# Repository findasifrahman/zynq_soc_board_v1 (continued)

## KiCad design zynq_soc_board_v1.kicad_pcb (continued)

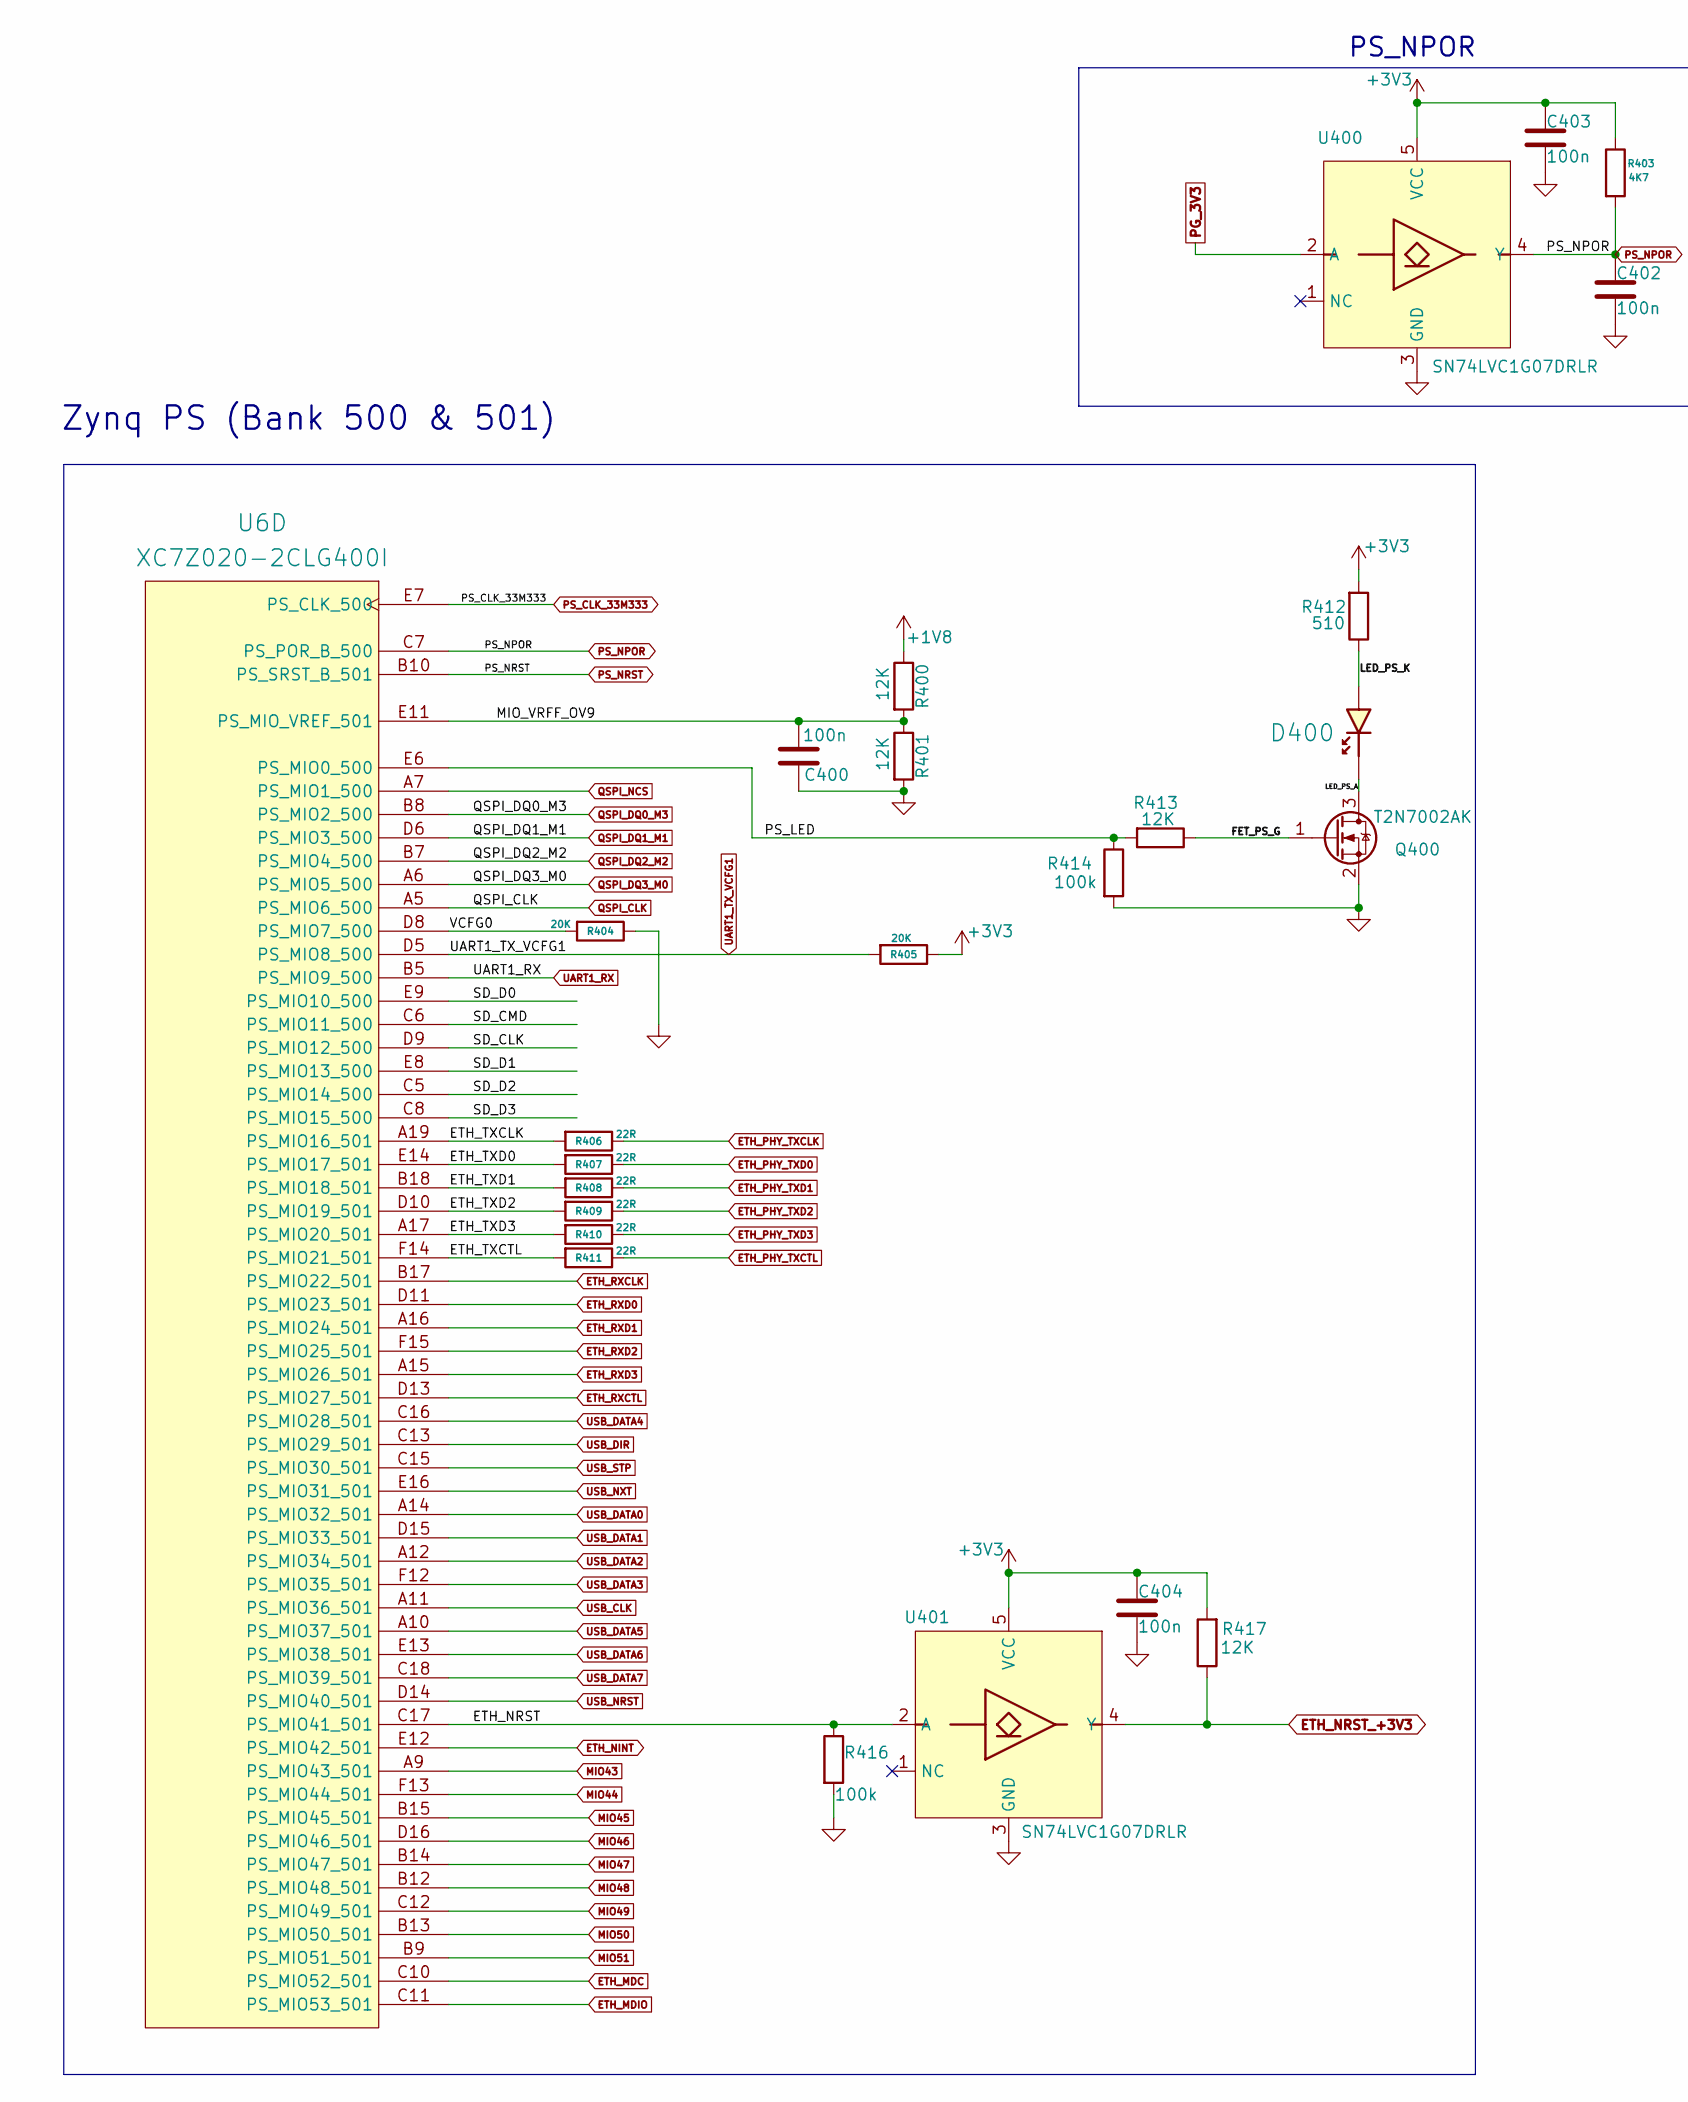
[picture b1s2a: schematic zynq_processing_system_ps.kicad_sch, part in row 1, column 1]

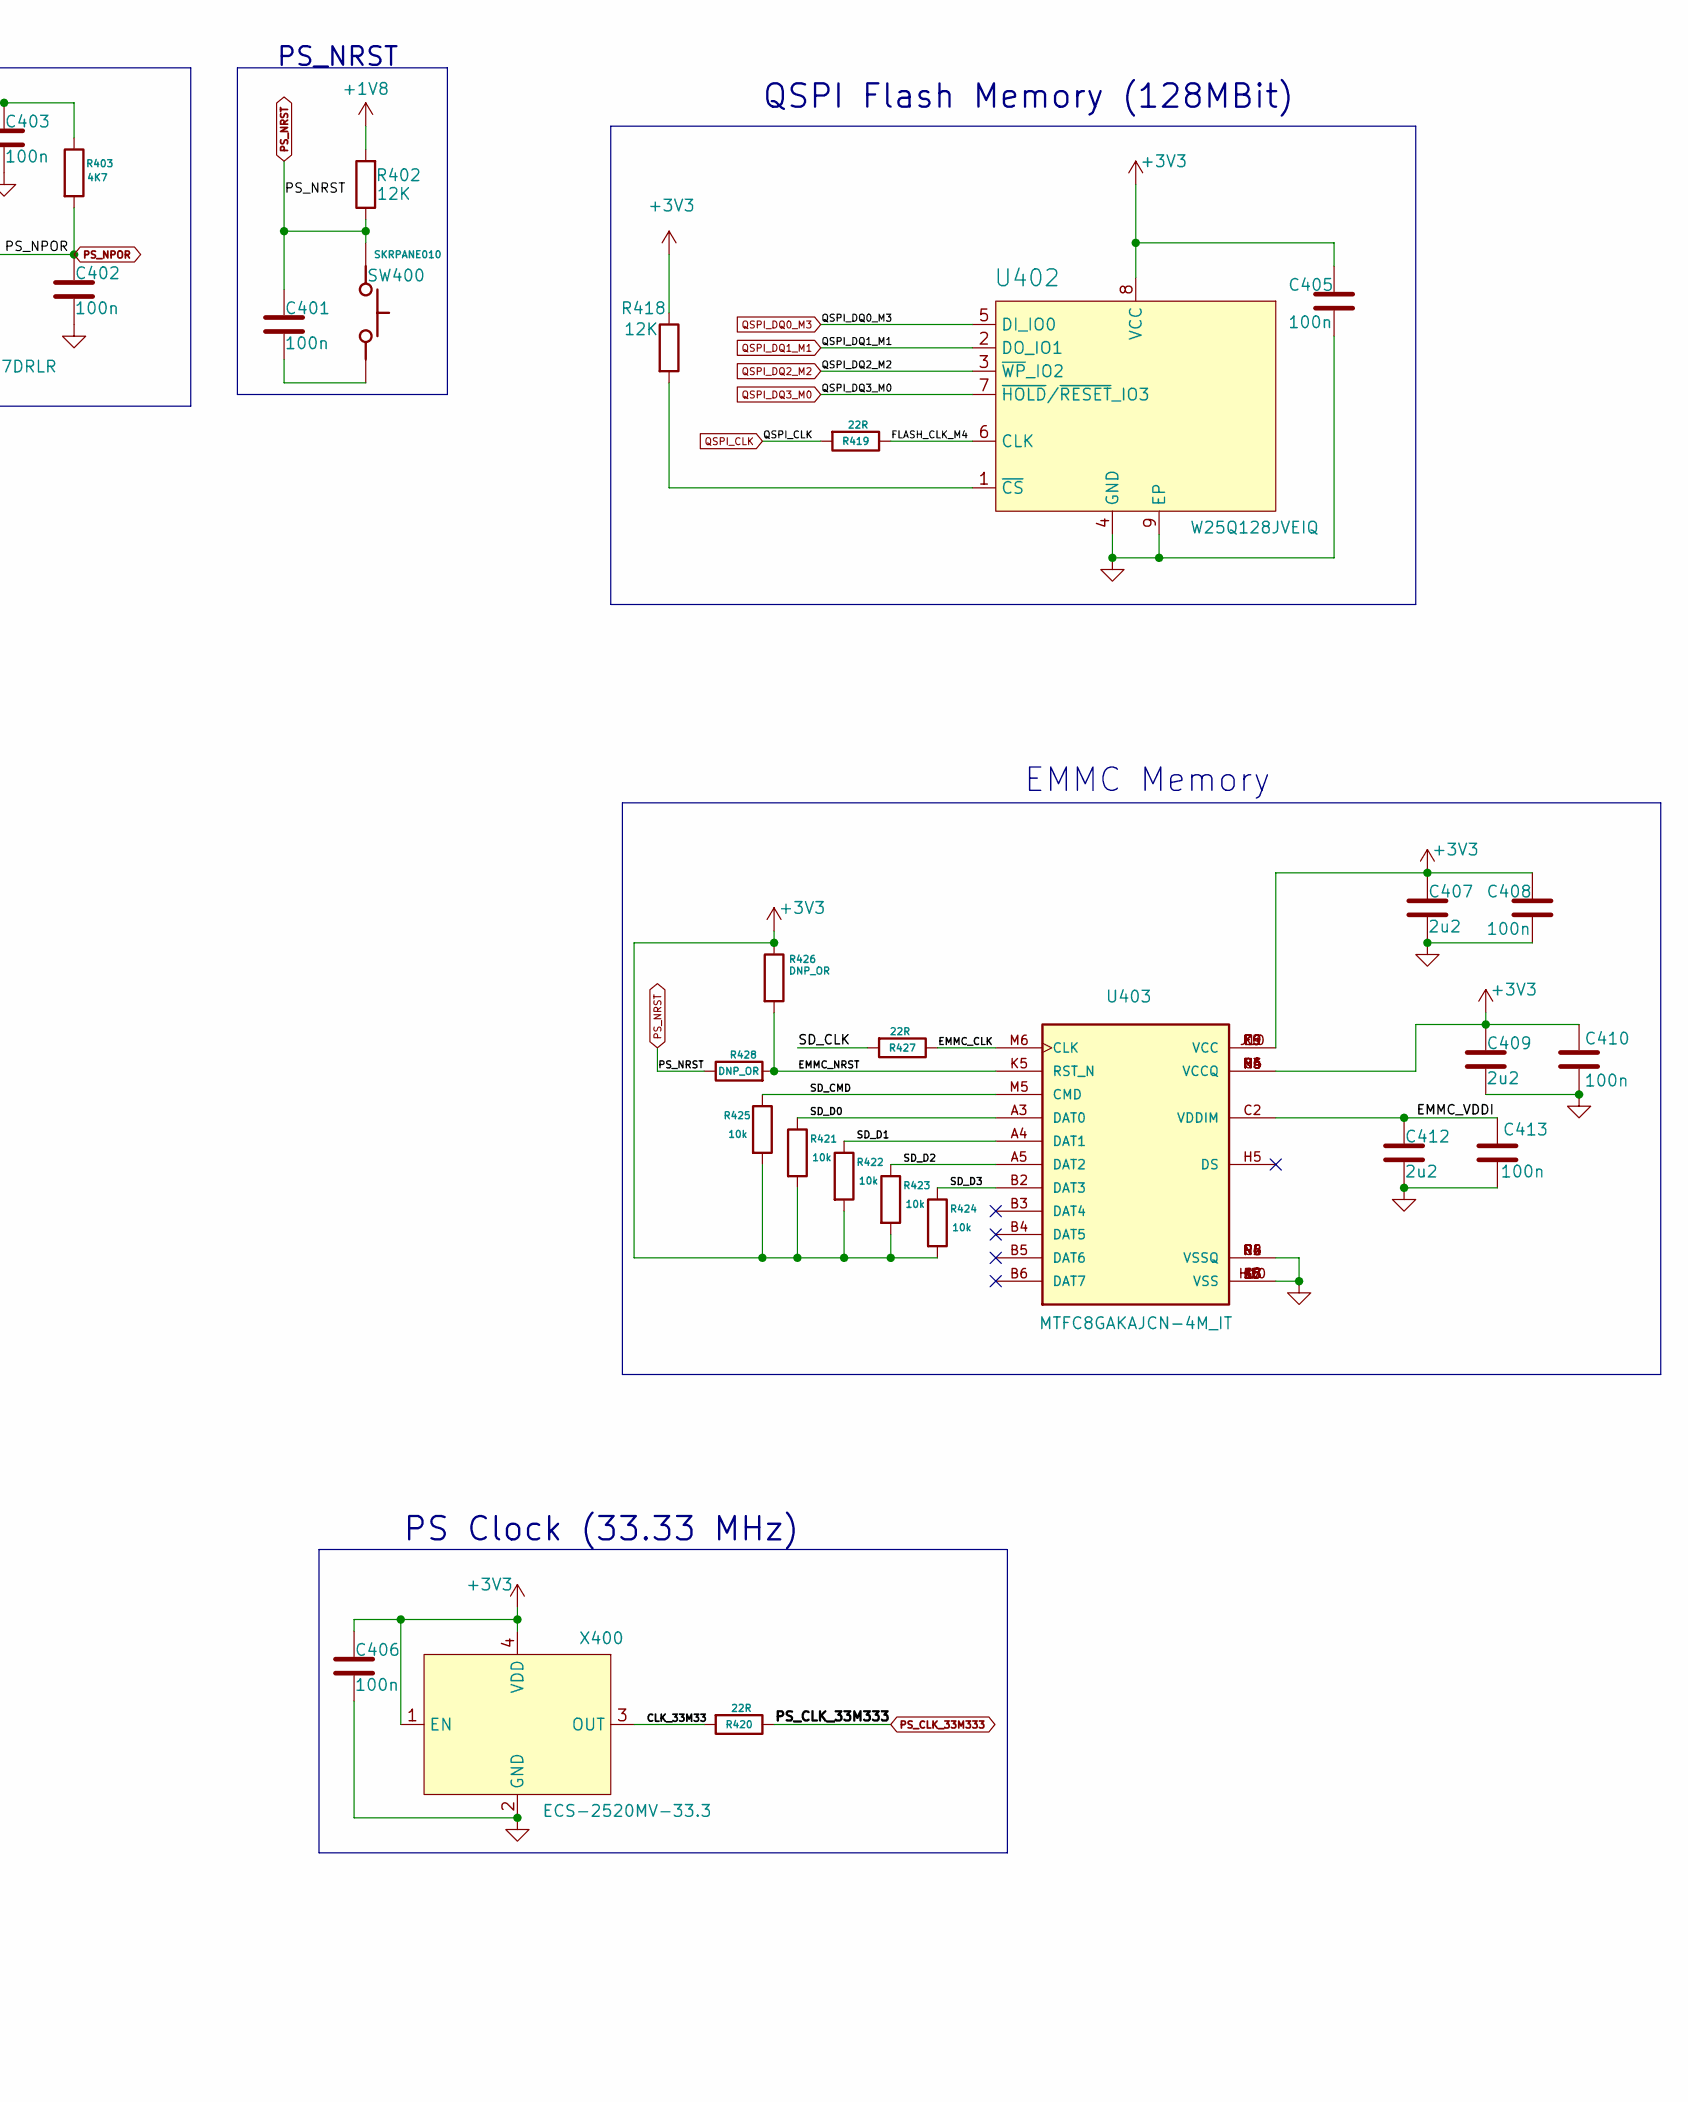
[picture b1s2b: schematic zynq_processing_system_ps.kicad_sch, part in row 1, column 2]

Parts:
C400, C401, C402, C403, C404, C405, C406, C408, C410, C413: 100n; C_0402_1005Metric; Manufacturer Part Number CL05B104KO5NNNC; LCSC C1525
C407, C409, C412: 2u2; C_0402_1005Metric; Manufacturer Part Number CL05A225MQ5NSNC; LCSC C12530
D400: RED; LED_0402_RED; Manufacturer Part Number NCD0402R1; LCSC C130719
Q400: T2N7002AK; SOT-23; Manufacturer Part Number T2N7002AK,LM; LCSC C516175
R400, R401, R402, R413, R417, R418: 12K; R_0402_1005Metric; Manufacturer Part Number 0402WGF1202TCE; LCSC C25752
R403: 4K7; R_0402_1005Metric; Manufacturer Part Number 0402WGF4701TCE; LCSC C25900
R404, R405: 20K; R0201; Manufacturer Part Number RC0201FR-0720KL; LCSC C295787
R406, R407, R408, R409, R410, R411, R419, R420, R427: 22R; R_0402_1005Metric; Manufacturer Part Number 0402WGF220JTCE; LCSC C25092
R412: 510; R_0402_1005Metric; Manufacturer Part Number RC-02W511JT; LCSC C1119
R414, R416: 100k; R_0402_1005Metric; Manufacturer Part Number 0402WGF1003TCE; LCSC C25741
R421, R422, R423, R424, R425: 10k; R_0402_1005Metric; Manufacturer Part Number 0402WGF1002TCE; LCSC C25744
R426, R428: DNP_OR; R_0402_1005Metric
SW400: SKRPANE010; Manufacturer Part Number SKRPANE010; LCSC C470426
U6: XC7Z020-2CLG400I; Xilinx_CLG400; PartNumber XC7Z010-1CLG400C; LCSC C569043
U400, U401: SN74LVC1G07DRLR; SOT-5; Manufacturer Part Number SN74LVC1G07DRLR; LCSC C183013
U402: W25Q128JVEIQ; WSON-8-8X6; Manufacturer Part Number W25Q128JVEIQ; LCSC C401662
U403: MTFC8GAKAJCN-4M_IT; FBGA-153_L13.0-W11.5-P0.50_KLMAG1JETD-B041; LCSC C395384
X400: ECS-2520MV-33.3; XTAL_2520; Manufacturer Part Number ECS-2520MV-333.3-BN-TR; LCSC C405468

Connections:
+1V8: R400.1, R402.2; also elsewhere on the board
+3V3: C403.1, C404.1, C405.1, C406.1, C407.1, C408.1, C409.1, C410.1, R403.1, R405.1, R412.2, R417.2, R418.1, R421.2, R422.2, R423.2, R424.2, R425.2, R426.1, U400.5 (VCC), U401.5 (VCC), U402.8 (VCC), U403.C6 (VCCQ), U403.E6 (VCC), U403.F5 (VCC), U403.J10 (VCC), U403.K9 (VCC), U403.M4 (VCCQ), U403.N4 (VCCQ), U403.P3 (VCCQ), U403.P5 (VCCQ), X400.1 (EN), X400.4 (VDD); also elsewhere on the board
/zynq_processing_system_ps/CLK_33M33: R420.2, X400.3 (OUT)
/zynq_processing_system_ps/EMMC_CLK: R427.1, U403.M6 (CLK)
/zynq_processing_system_ps/EMMC_NRST: R426.2, R428.2, U403.K5 (RST_N)
/zynq_processing_system_ps/EMMC_VDDI: C412.1, C413.1, U403.C2 (VDDIM)
/zynq_processing_system_ps/ETH_NRST: R416.1, U6.C17 (PS_MIO41_501), U401.2 (A)
/zynq_processing_system_ps/ETH_TXCLK: R406.2, U6.A19 (PS_MIO16_501)
/zynq_processing_system_ps/ETH_TXCTL: R411.2, U6.F14 (PS_MIO21_501)
/zynq_processing_system_ps/ETH_TXD0: R407.2, U6.E14 (PS_MIO17_501)
/zynq_processing_system_ps/ETH_TXD1: R408.2, U6.B18 (PS_MIO18_501)
/zynq_processing_system_ps/ETH_TXD2: R409.2, U6.D10 (PS_MIO19_501)
/zynq_processing_system_ps/ETH_TXD3: R410.2, U6.A17 (PS_MIO20_501)
/zynq_processing_system_ps/FET_PS_G: Q400.1 (G), R413.1
/zynq_processing_system_ps/FLASH_CLK_M4: R419.1, U402.6 (CLK)
/zynq_processing_system_ps/LED_PS_A: D400.K, Q400.3 (D)
/zynq_processing_system_ps/LED_PS_K: D400.A, R412.1
/zynq_processing_system_ps/MIO_VRFF_OV9: C400.2, R400.2, R401.1, U6.E11 (PS_MIO_VREF_501)
/zynq_processing_system_ps/PS_LED: R413.2, R414.1, U6.E6 (PS_MIO0_500)
/zynq_processing_system_ps/SD_CLK: R427.2, U6.D9 (PS_MIO12_500)
/zynq_processing_system_ps/SD_CMD: R425.1, U6.C6 (PS_MIO11_500), U403.M5 (CMD)
/zynq_processing_system_ps/SD_D0: R421.1, U6.E9 (PS_MIO10_500), U403.A3 (DAT0)
/zynq_processing_system_ps/SD_D1: R422.1, U6.E8 (PS_MIO13_500), U403.A4 (DAT1)
/zynq_processing_system_ps/SD_D2: R423.1, U6.C5 (PS_MIO14_500), U403.A5 (DAT2)
/zynq_processing_system_ps/SD_D3: R424.1, U6.C8 (PS_MIO15_500), U403.B2 (DAT3)
/zynq_processing_system_ps/VCFG0: R404.2, U6.D8 (PS_MIO7_500)
ETH_MDC: U6.C10 (PS_MIO52_501); also elsewhere on the board
ETH_MDIO: U6.C11 (PS_MIO53_501); also elsewhere on the board
ETH_NINT: U6.E12 (PS_MIO42_501); also elsewhere on the board
ETH_NRST_+3V3: R417.1, U401.4 (Y); also elsewhere on the board
ETH_PHY_TXCLK: R406.1; also elsewhere on the board
ETH_PHY_TXCTL: R411.1; also elsewhere on the board
ETH_PHY_TXD0: R407.1; also elsewhere on the board
ETH_PHY_TXD1: R408.1; also elsewhere on the board
ETH_PHY_TXD2: R409.1; also elsewhere on the board
ETH_PHY_TXD3: R410.1; also elsewhere on the board
ETH_RXCLK: U6.B17 (PS_MIO22_501); also elsewhere on the board
ETH_RXCTL: U6.D13 (PS_MIO27_501); also elsewhere on the board
ETH_RXD0: U6.D11 (PS_MIO23_501); also elsewhere on the board
ETH_RXD1: U6.A16 (PS_MIO24_501); also elsewhere on the board
ETH_RXD2: U6.F15 (PS_MIO25_501); also elsewhere on the board
ETH_RXD3: U6.A15 (PS_MIO26_501); also elsewhere on the board
GND: C400.1, C402.2, C403.2, C404.2, C405.2, C406.2, C407.2, C408.2, C409.2, C410.2, C412.2, C413.2, Q400.2 (S), R401.2, R404.1, R414.2, R416.2, U400.3 (GND), U401.3 (GND), U402.4 (GND), U402.9 (EP), U403.A6 (VSS), U403.C4 (VSSQ), U403.E7 (VSS), U403.G5 (VSS), U403.H10 (VSS), U403.J5 (VSS), U403.K8 (VSS), U403.N2 (VSSQ), U403.N5 (VSSQ), U403.P4 (VSSQ), U403.P6 (VSSQ), X400.2 (GND); also elsewhere on the board
MIO43: U6.A9 (PS_MIO43_501)
MIO44: U6.F13 (PS_MIO44_501)
MIO45: U6.B15 (PS_MIO45_501)
MIO46: U6.D16 (PS_MIO46_501)
MIO47: U6.B14 (PS_MIO47_501)
MIO48: U6.B12 (PS_MIO48_501)
MIO49: U6.C12 (PS_MIO49_501); also elsewhere on the board
MIO50: U6.B13 (PS_MIO50_501); also elsewhere on the board
MIO51: U6.B9 (PS_MIO51_501); also elsewhere on the board
unnamed: C401.2, SW400.34
unnamed: R418.2, U402.1 (~CS)
PG_3V3: U400.2 (A); also elsewhere on the board
PS_CLK_33M333: R420.1, U6.E7 (PS_CLK_500)
PS_NPOR: C402.1, R403.2, U6.C7 (PS_POR_B_500), U400.4 (Y); also elsewhere on the board
PS_NRST: C401.1, R402.1, R428.1, SW400.12, U6.B10 (PS_SRST_B_501)
QSPI_CLK: R419.2, U6.A5 (PS_MIO6_500)
QSPI_DQ0_M3: U6.B8 (PS_MIO2_500), U402.5 (DI_IO0); also elsewhere on the board
QSPI_DQ1_M1: U6.D6 (PS_MIO3_500), U402.2 (DO_IO1); also elsewhere on the board
QSPI_DQ2_M2: U6.B7 (PS_MIO4_500), U402.3 (~WP_IO2); also elsewhere on the board
QSPI_DQ3_M0: U6.A6 (PS_MIO5_500), U402.7 (~HOLD/~RESET_IO3); also elsewhere on the board
QSPI_NCS: U6.A7 (PS_MIO1_500)
UART1_RX: U6.B5 (PS_MIO9_500); also elsewhere on the board
UART1_TX_VCFG1: R405.2, U6.D5 (PS_MIO8_500); also elsewhere on the board
USB_CLK: U6.A11 (PS_MIO36_501); also elsewhere on the board
USB_DATA0: U6.A14 (PS_MIO32_501); also elsewhere on the board
USB_DATA1: U6.D15 (PS_MIO33_501); also elsewhere on the board
USB_DATA2: U6.A12 (PS_MIO34_501); also elsewhere on the board
USB_DATA3: U6.F12 (PS_MIO35_501); also elsewhere on the board
USB_DATA4: U6.C16 (PS_MIO28_501); also elsewhere on the board
USB_DATA5: U6.A10 (PS_MIO37_501); also elsewhere on the board
USB_DATA6: U6.E13 (PS_MIO38_501); also elsewhere on the board
USB_DATA7: U6.C18 (PS_MIO39_501); also elsewhere on the board
USB_DIR: U6.C13 (PS_MIO29_501); also elsewhere on the board
USB_NRST: U6.D14 (PS_MIO40_501); also elsewhere on the board
USB_NXT: U6.E16 (PS_MIO31_501); also elsewhere on the board
USB_STP: U6.C15 (PS_MIO30_501); also elsewhere on the board

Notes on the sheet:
PS_NPOR
QSPI Flash Memory (128MBit)
EMMC Memory
Zynq PS (Bank 500 & 501)
PS_NRST
PS Clock (33.33 MHz)

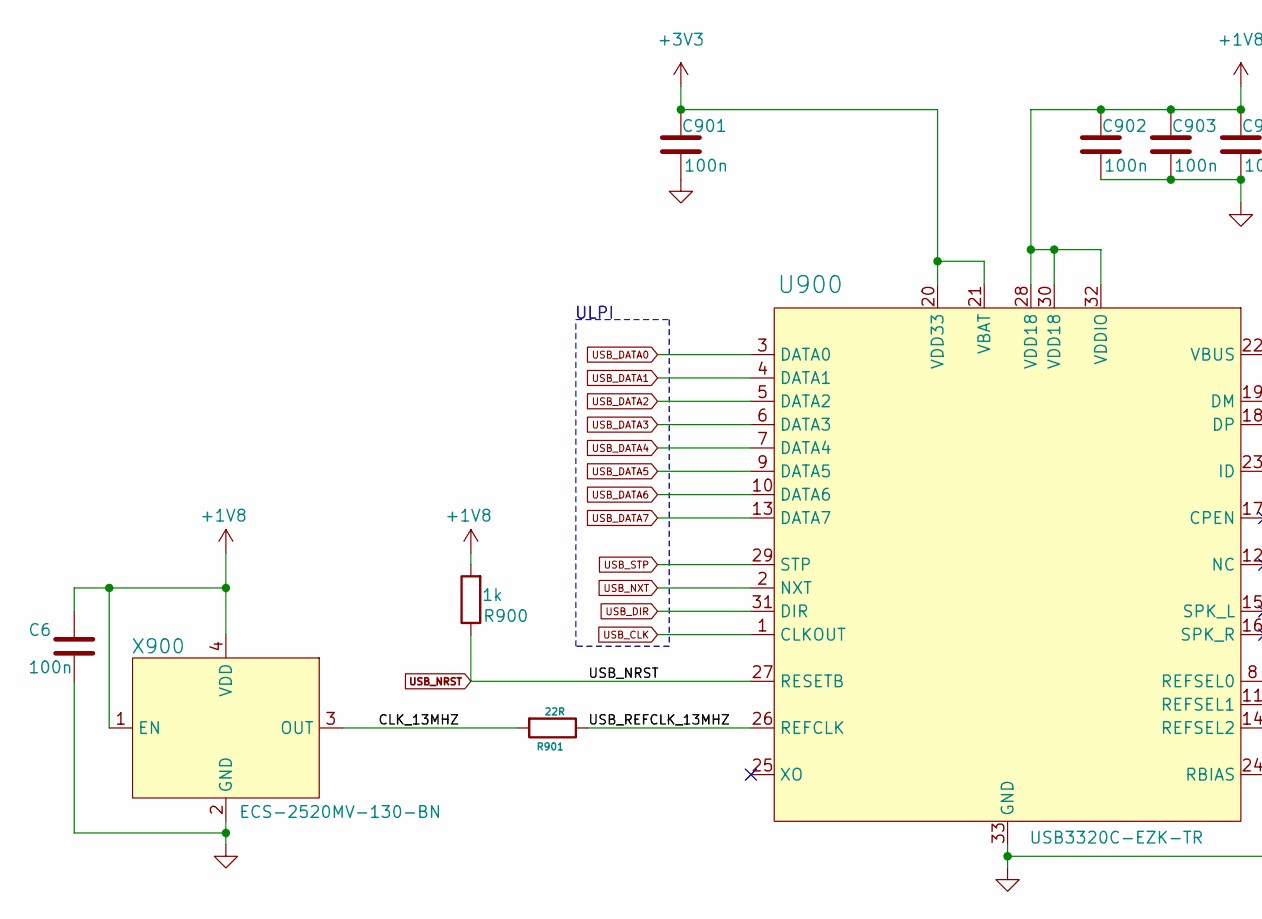
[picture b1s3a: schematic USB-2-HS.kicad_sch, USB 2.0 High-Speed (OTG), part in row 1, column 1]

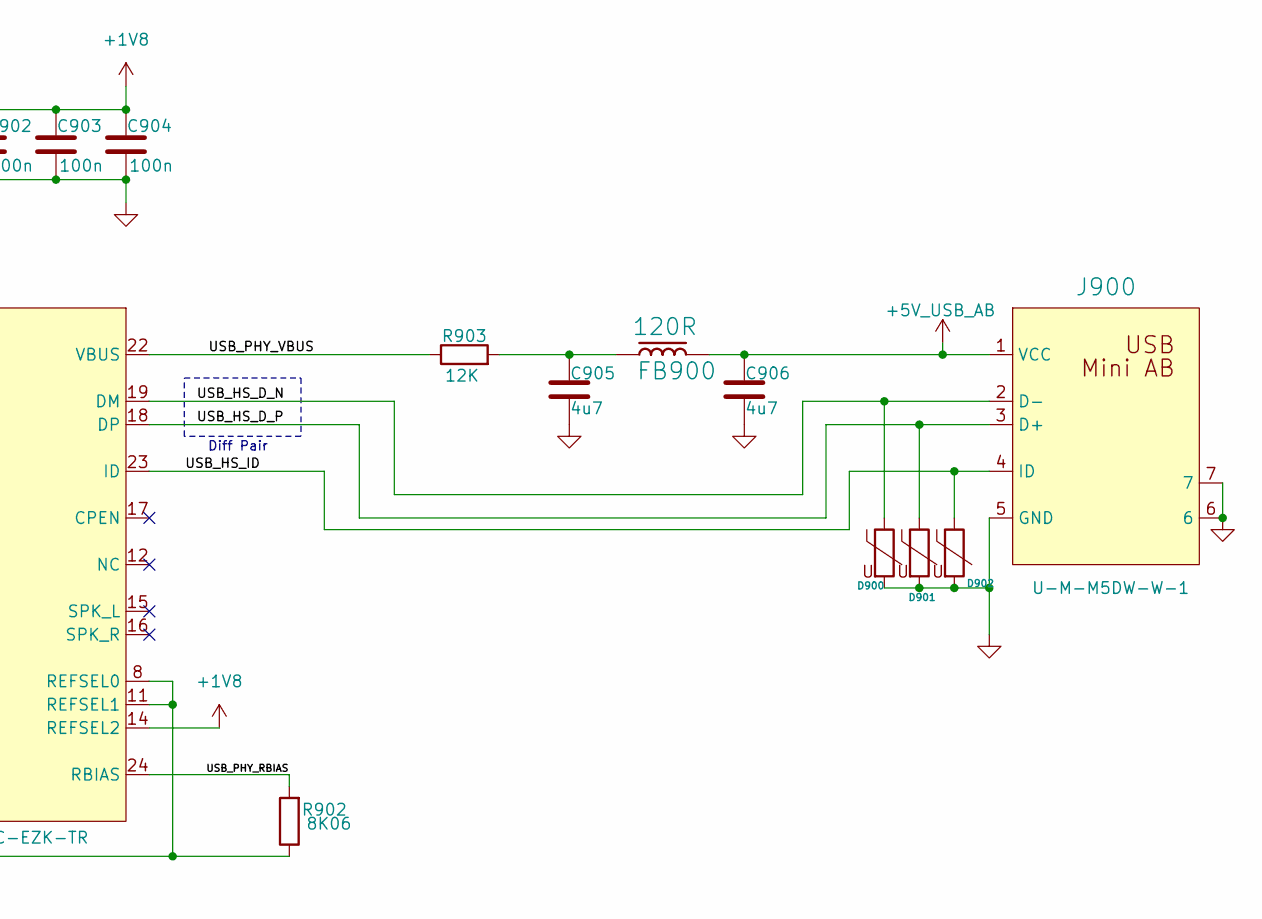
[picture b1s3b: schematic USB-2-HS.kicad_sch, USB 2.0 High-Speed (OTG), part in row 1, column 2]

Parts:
C6, C901, C902, C903, C904: 100n; C_0402_1005Metric; Manufacturer Part Number CL05B104KO5NNNC; LCSC C1525
C905, C906: 4u7; C_0402_1005Metric; Manufacturer Part Number CL05A475MP5NRNC; LCSC C23733
D900, D901, D902: Varistor; C0402; Manufacturer Part Number CG0402MLU-3.3G; LCSC C2655393
FB900: 120R; FB_0402; Manufacturer Part Number GZ1005D121TF; LCSC C38480
J900: U-M-M5DW-W-1; MINI-USB-TH_U-M-M5DW-W-1; Manufacturer Part Number U-M-M5DW-W-1; LCSC C530648
R900: 1k; R_0402_1005Metric; Manufacturer Part Number 0402WGF1001TCE; LCSC C11702
R901: 22R; R_0402_1005Metric; Manufacturer Part Number 0402WGF220JTCE; LCSC C25092
R902: 8K06; R_0402_1005Metric; Manufacturer Part Number 0402WGF8061TCE; LCSC C25923
R903: 12K; R_0402_1005Metric; Manufacturer Part Number 0402WGF1202TCE; LCSC C25752
U900: USB3320C-EZK-TR; QFN-32-5x5x0.85mm; Manufacturer Part Number USB3320C-EZK-TR; LCSC C132156
X900: ECS-2520MV-130-BN; XTAL_2520; Manufacturer Part Number ECS-2520MV-130-BN-TR; LCSC C2613032

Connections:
+1V8: C6.1, C902.1, C903.1, C904.1, R900.2, U900.14 (REFSEL2), U900.28 (VDD18), U900.30 (VDD18), U900.32 (VDDIO), X900.1 (EN), X900.4 (VDD); also elsewhere on the board
+3V3: C901.1, U900.20 (VDD33), U900.21 (VBAT); also elsewhere on the board
+5V_USB_AB: C906.1, FB900.2, J900.1 (VCC)
/USB-2-HS/CLK_13MHZ: R901.2, X900.3 (OUT)
/USB-2-HS/USB_HS_D_N: D900.1, J900.2 (D-), U900.19 (DM)
/USB-2-HS/USB_HS_D_P: D901.1, J900.3 (D+), U900.18 (DP)
/USB-2-HS/USB_HS_ID: D902.1, J900.4 (ID), U900.23 (ID)
/USB-2-HS/USB_PHY_RBIAS: R902.2, U900.24 (RBIAS)
/USB-2-HS/USB_PHY_VBUS: R903.1, U900.22 (VBUS)
/USB-2-HS/USB_REFCLK_13MHZ: R901.1, U900.26 (REFCLK)
GND: C6.2, C901.2, C902.2, C903.2, C904.2, C905.2, C906.2, D900.2, D901.2, D902.2, J900.5 (GND), J900.6, J900.7, R902.1, U900.8 (REFSEL0), U900.11 (REFSEL1), U900.33 (GND), X900.2 (GND); also elsewhere on the board
unnamed: C905.1, FB900.1, R903.2
USB_CLK: U900.1 (CLKOUT); also elsewhere on the board
USB_DATA0: U900.3 (DATA0); also elsewhere on the board
USB_DATA1: U900.4 (DATA1); also elsewhere on the board
USB_DATA2: U900.5 (DATA2); also elsewhere on the board
USB_DATA3: U900.6 (DATA3); also elsewhere on the board
USB_DATA4: U900.7 (DATA4); also elsewhere on the board
USB_DATA5: U900.9 (DATA5); also elsewhere on the board
USB_DATA6: U900.10 (DATA6); also elsewhere on the board
USB_DATA7: U900.13 (DATA7); also elsewhere on the board
USB_DIR: U900.31 (DIR); also elsewhere on the board
USB_NRST: R900.1, U900.27 (RESETB); also elsewhere on the board
USB_NXT: U900.2 (NXT); also elsewhere on the board
USB_STP: U900.29 (STP); also elsewhere on the board

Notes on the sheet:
ULPI
Diff Pair

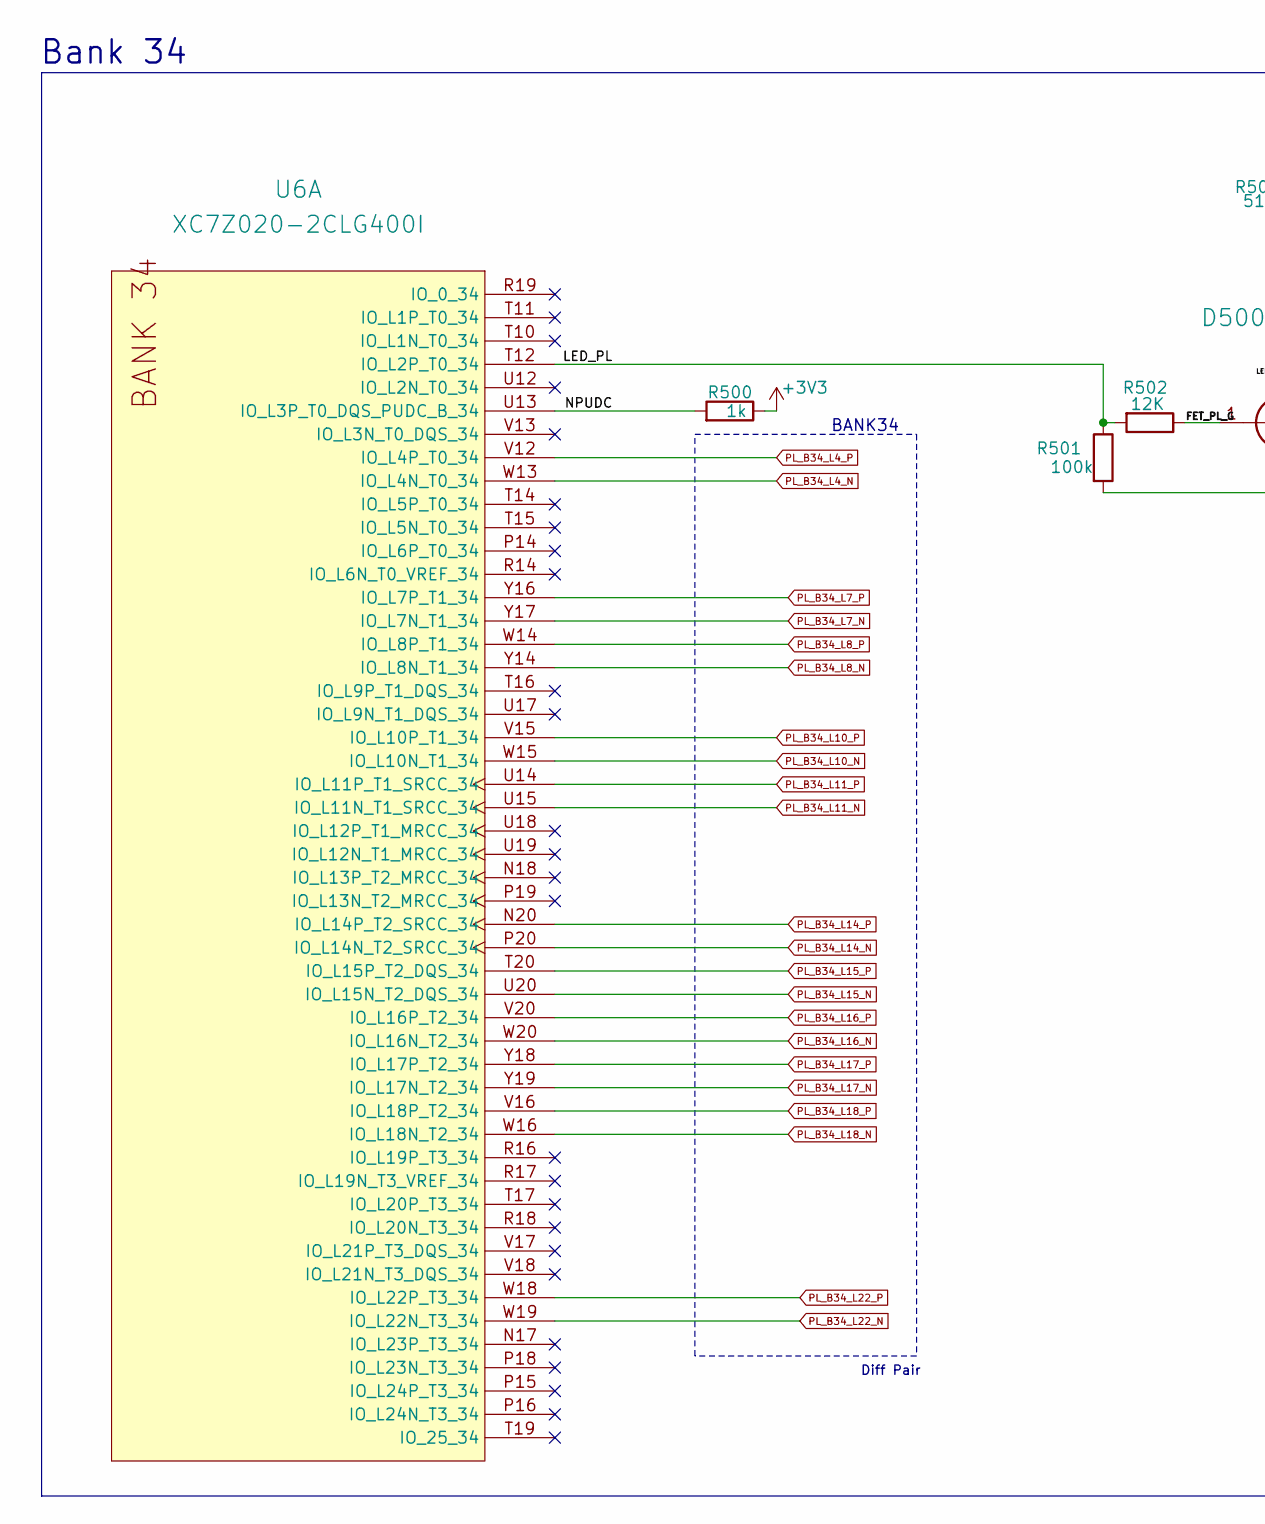
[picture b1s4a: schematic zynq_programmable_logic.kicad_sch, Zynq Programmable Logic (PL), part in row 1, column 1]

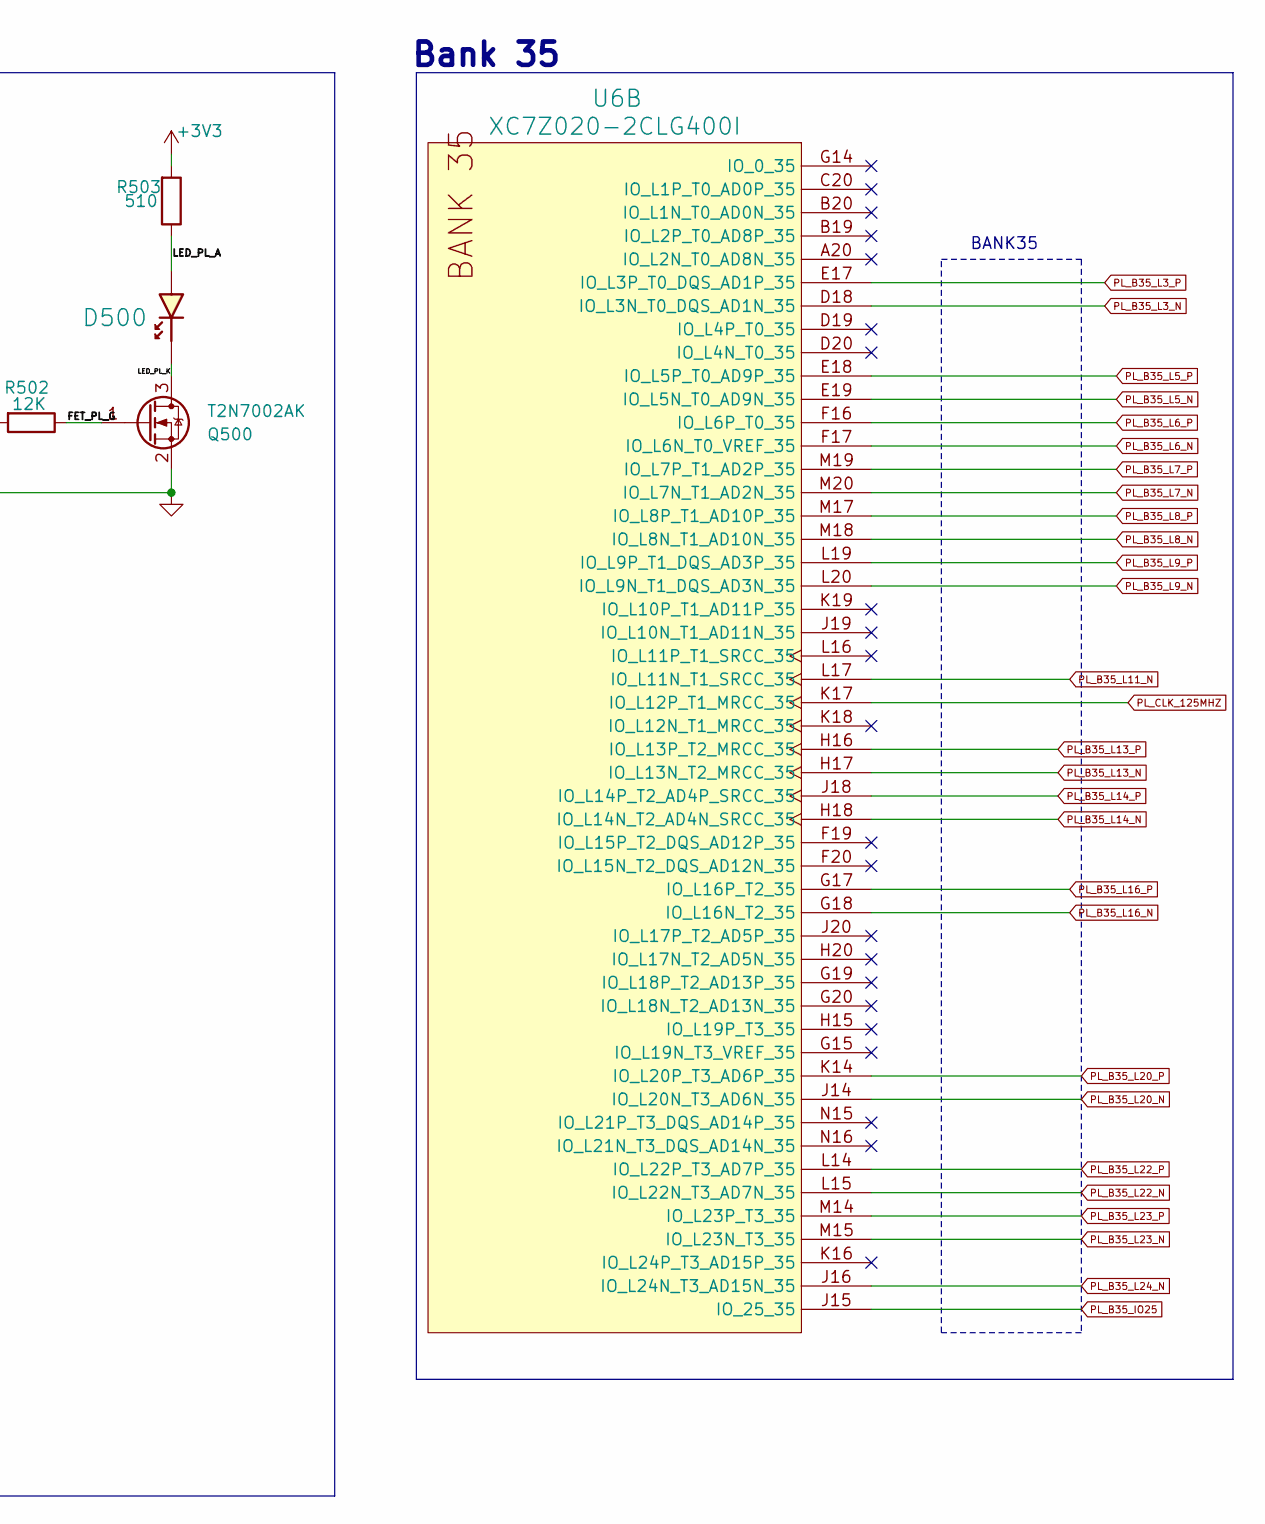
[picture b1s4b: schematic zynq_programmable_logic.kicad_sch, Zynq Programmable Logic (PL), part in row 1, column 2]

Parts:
D500: RED; LED_0402_RED; Manufacturer Part Number NCD0402R1; LCSC C130719
Q500: T2N7002AK; SOT-23; Manufacturer Part Number T2N7002AK,LM; LCSC C516175
R500: 1k; R_0402_1005Metric; Manufacturer Part Number 0402WGF1001TCE; LCSC C11702
R501: 100k; R_0402_1005Metric; Manufacturer Part Number 0402WGF1003TCE; LCSC C25741
R502: 12K; R_0402_1005Metric; Manufacturer Part Number 0402WGF1202TCE; LCSC C25752
R503: 510; R_0402_1005Metric; Manufacturer Part Number RC-02W511JT; LCSC C1119
U6: XC7Z020-2CLG400I; Xilinx_CLG400; PartNumber XC7Z010-1CLG400C; LCSC C569043

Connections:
+3V3: R500.1, R503.2; also elsewhere on the board
/zynq_programmable_logic/FET_PL_G: Q500.1 (G), R502.1
/zynq_programmable_logic/LED_PL: R501.1, R502.2, U6.T12 (IO_L2P_T0_34)
/zynq_programmable_logic/LED_PL_A: D500.A, R503.1
/zynq_programmable_logic/LED_PL_K: D500.K, Q500.3 (D)
/zynq_programmable_logic/NPUDC: R500.2, U6.U13 (IO_L3P_T0_DQS_PUDC_B_34)
GND: Q500.2 (S), R501.2; also elsewhere on the board
PL_B34_L4_N: U6.W13 (IO_L4N_T0_34); also elsewhere on the board
PL_B34_L4_P: U6.V12 (IO_L4P_T0_34); also elsewhere on the board
PL_B34_L7_N: U6.Y17 (IO_L7N_T1_34); also elsewhere on the board
PL_B34_L7_P: U6.Y16 (IO_L7P_T1_34); also elsewhere on the board
PL_B34_L8_N: U6.Y14 (IO_L8N_T1_34); also elsewhere on the board
PL_B34_L8_P: U6.W14 (IO_L8P_T1_34); also elsewhere on the board
PL_B34_L10_N: U6.W15 (IO_L10N_T1_34); also elsewhere on the board
PL_B34_L10_P: U6.V15 (IO_L10P_T1_34); also elsewhere on the board
PL_B34_L11_N: U6.U15 (IO_L11N_T1_SRCC_34); also elsewhere on the board
PL_B34_L11_P: U6.U14 (IO_L11P_T1_SRCC_34); also elsewhere on the board
PL_B34_L14_N: U6.P20 (IO_L14N_T2_SRCC_34); also elsewhere on the board
PL_B34_L14_P: U6.N20 (IO_L14P_T2_SRCC_34); also elsewhere on the board
PL_B34_L15_N: U6.U20 (IO_L15N_T2_DQS_34); also elsewhere on the board
PL_B34_L15_P: U6.T20 (IO_L15P_T2_DQS_34); also elsewhere on the board
PL_B34_L16_N: U6.W20 (IO_L16N_T2_34); also elsewhere on the board
PL_B34_L16_P: U6.V20 (IO_L16P_T2_34); also elsewhere on the board
PL_B34_L17_N: U6.Y19 (IO_L17N_T2_34); also elsewhere on the board
PL_B34_L17_P: U6.Y18 (IO_L17P_T2_34); also elsewhere on the board
PL_B34_L18_N: U6.W16 (IO_L18N_T2_34); also elsewhere on the board
PL_B34_L18_P: U6.V16 (IO_L18P_T2_34); also elsewhere on the board
PL_B34_L22_N: U6.W19 (IO_L22N_T3_34); also elsewhere on the board
PL_B34_L22_P: U6.W18 (IO_L22P_T3_34); also elsewhere on the board
PL_B35_IO25: U6.J15 (IO_25_35); also elsewhere on the board
PL_B35_L3_N: U6.D18 (IO_L3N_T0_DQS_AD1N_35); also elsewhere on the board
PL_B35_L3_P: U6.E17 (IO_L3P_T0_DQS_AD1P_35); also elsewhere on the board
PL_B35_L5_N: U6.E19 (IO_L5N_T0_AD9N_35); also elsewhere on the board
PL_B35_L5_P: U6.E18 (IO_L5P_T0_AD9P_35); also elsewhere on the board
PL_B35_L6_N: U6.F17 (IO_L6N_T0_VREF_35); also elsewhere on the board
PL_B35_L6_P: U6.F16 (IO_L6P_T0_35); also elsewhere on the board
PL_B35_L7_N: U6.M20 (IO_L7N_T1_AD2N_35); also elsewhere on the board
PL_B35_L7_P: U6.M19 (IO_L7P_T1_AD2P_35); also elsewhere on the board
PL_B35_L8_N: U6.M18 (IO_L8N_T1_AD10N_35); also elsewhere on the board
PL_B35_L8_P: U6.M17 (IO_L8P_T1_AD10P_35); also elsewhere on the board
PL_B35_L9_N: U6.L20 (IO_L9N_T1_DQS_AD3N_35); also elsewhere on the board
PL_B35_L9_P: U6.L19 (IO_L9P_T1_DQS_AD3P_35); also elsewhere on the board
PL_B35_L11_N: U6.L17 (IO_L11N_T1_SRCC_35); also elsewhere on the board
PL_B35_L13_N: U6.H17 (IO_L13N_T2_MRCC_35); also elsewhere on the board
PL_B35_L13_P: U6.H16 (IO_L13P_T2_MRCC_35); also elsewhere on the board
PL_B35_L14_N: U6.H18 (IO_L14N_T2_AD4N_SRCC_35); also elsewhere on the board
PL_B35_L14_P: U6.J18 (IO_L14P_T2_AD4P_SRCC_35); also elsewhere on the board
PL_B35_L16_N: U6.G18 (IO_L16N_T2_35); also elsewhere on the board
PL_B35_L16_P: U6.G17 (IO_L16P_T2_35); also elsewhere on the board
PL_B35_L20_N: U6.J14 (IO_L20N_T3_AD6N_35); also elsewhere on the board
PL_B35_L20_P: U6.K14 (IO_L20P_T3_AD6P_35); also elsewhere on the board
PL_B35_L22_N: U6.L15 (IO_L22N_T3_AD7N_35); also elsewhere on the board
PL_B35_L22_P: U6.L14 (IO_L22P_T3_AD7P_35); also elsewhere on the board
PL_B35_L23_N: U6.M15 (IO_L23N_T3_35); also elsewhere on the board
PL_B35_L23_P: U6.M14 (IO_L23P_T3_35); also elsewhere on the board
PL_B35_L24_N: U6.J16 (IO_L24N_T3_AD15N_35); also elsewhere on the board
PL_CLK_125MHZ: U6.K17 (IO_L12P_T1_MRCC_35); also elsewhere on the board

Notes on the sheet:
Bank 35
BANK34
Diff Pair
Bank 34
BANK35
